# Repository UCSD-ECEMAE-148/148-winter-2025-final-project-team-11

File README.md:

# <div align="center">Autonomous Police Car</div>

### <div align="center"> ECE 148 Final Project </div>

#### <div align="center"> Team 11 Winter 2025 </div>

<div align="center">
    
</div>

## Table of Contents

  <ol>
    <li><a href="#team-members">Team Members</a></li>
    <li><a href="#abstract">Abstract</a></li>
    <li><a href="#what-we-promised">What We Promised</a></li>
    <li><a href="#accomplishments">Accomplishments</a></li>
    <li><a href="#challenges">Challenges</a></li>
    <li><a href="#final-project-videos">Final Project Videos</a></li>
    <li><a href="#hardware">Hardware</a></li>
    <li><a href="#software">Software</a></li>
        <ul>
            <li><a href="#slam-simultaneous-localization-and-mapping">SLAM (Simultaneous Localization and Mapping)</a></li>
            <li><a href="#obstacle-avoidance">Obstacle Avoidance</a></li>
        </ul>
    <li><a href="#gantt-chart">Gantt Chart</a></li>
    <li><a href="#course-deliverables">Course Deliverables</a></li>
    <li><a href="#project-reproduction">Project Reproduction</a></li>
    <li><a href="#acknowledgements">Acknowledgements</a></li>
  </ol>

<hr>

## Team Members

- MingWei Yeoh - ECE - 2025
- Trevor
- Minh Quach
- Jose

<hr>

## Abstract

An realistic looking autonomous car that can activate lights when it detects a speeding car and autonomously pull it over or initiate a chase.

Past MAE projects haven’t tried to use car following for a real task, nor make their autonomous car LOOK like an actual car.
Mechanically it will be a challenge to mount all the electronics inside of a small car body.

<hr>

## What We Promised

### Must Have

- LEDs
- Communication between LED controller and Jetson
- Body shell Mounting
- Chase the car
- Yolo running on OAK-D Camera

### Nice to Have

- Cool PCB
- Clean Electronics mounting
- A Siren
<hr>

## Accomplishments

- Follows car
- LEDs work great
- 150A Soft start power switch works great
<hr>

## Challenges

- Jetson not connecting to Wifi
- ROS2 not configured correctly to run our nodes
- I2C reaching bugged state
<hr>

## Final Project Videos

<hr>

## Hardware

Link to the OnShape [CAD](https://cad.onshape.com/documents/6c423dcbeb2588a9d7785133/w/5859bc8aee528f453679c661/e/83214a9dc768b66fa2069d19?renderMode=0&uiState=67d3caa0a720212af3f91fbd)

- **Green** - Body shell mounting method. It uses 8x3mm magnets.
- **Purple** - Reference geometry from the car
- **Black** - Structural 3D Printed pieces
- **Orange** - 3D Printed Spacers

The design is super clean and allows the body shell to easily cover all the electronics.

**Additional Hardware Necessary**

- Custom LED driver PCB
- Custom LED module
- 8x3mm Magnets
- 3mm bolts
- Body shell

## PCB

### High Level Overview

- Embedded EPS32S3
- USB C Port
- Anti spark power switch capable of 150 A
- Buzzer (for siren)
- 2x High Powered led driver
- 3x WS2815 Led Controllers
- Communication with Jetson via I2C
- 3 Spare GPIOs (if needed)
- Onboard VBAT -> 3V3 Buck regulator

**Power**
Snippet from the schematic. 3 Low RDson PMOS' act like the switch. When the on button is pressed, the 4s Lipo gets fed into the onboard buck regulator to power the microcontroller.

### Assembly

Hand Assembled. Theres a lot of parts

### Bringup

**LEDS**

</br>

**I2C**
ESP32 acts as a peripheral device with address 0x55. It takes in a 2 byte command. 0x00 and 0x11.
0x00 Turns on LEDs and 0x11 turns off LEDs.

## Software - Robocar Visual Pursuit Package

A ROS2 package for autonomous vehicle pursuit using computer vision and DepthAI. This package enables a robocar to detect and follow another vehicle using visual tracking.

### Table of Contents

- [Features](#features)
- [Prerequisites](#prerequisites)
- [Installation](#installation)
- [Nodes](#nodes)
  - [Car Detection Node](#car-detection-node)
  - [Lane Guidance Node](#lane-guidance-node)
  - [Parameter Tuner Node](#parameter-tuner-node)
- [Topics](#topics)
- [Launch Files](#launch-files)
- [Parameter Tuning](#parameter-tuning)
- [Troubleshooting](#troubleshooting)
- [Configuration Files](#configuration-files)

### Features

- Real-time car detection using YOLO and DepthAI
- Adaptive PID-based steering control
- Dynamic throttle management
- Real-time parameter tuning interface
- Parameter persistence across launches
- Robust tracking with lost-frame handling

### Prerequisites

- ROS2
- DepthAI
- OpenCV
- Python 3.8+

### Installation

1. Clone this repository into your ROS2 workspace:

```bash
cd ~/ros2_ws/src
git clone <repository_url> robocar_visual_pursuit_pkg
```

2. Install dependencies:

```bash
cd ~/ros2_ws
rosdep install --from-paths src --ignore-src -r -y
```

3. Build the package:

```bash
colcon build --packages-select robocar_visual_pursuit_pkg
```

### Nodes

#### Car Detection Node

The car detection node uses YOLO and DepthAI to detect vehicles in the camera feed and calculate their position relative to the robot.

**Parameters:**

- `confidence_threshold` (0.0-1.0): Confidence threshold for car detection
- `camera_centerline` (0.0-1.0): Normalized position of camera centerline
- `error_threshold` (0.0-1.0): Error threshold for steering control
- `iou_threshold` (0.0-1.0): IOU threshold for object detection
- `max_lost_frames` (0-30): Maximum number of frames to track lost object

**Topics:**

- Subscribes: `/camera/color/image_raw` (sensor_msgs/Image)
- Publishes: `/centroid` (std_msgs/Float32)

#### Lane Guidance Node

The lane guidance node implements PID control for steering and adaptive throttle management based on tracking error.

**Parameters:**

- `Kp_steering` (0.0-5.0): Proportional gain for steering control
- `Ki_steering` (0.0-2.0): Integral gain for steering control
- `Kd_steering` (0.0-2.0): Derivative gain for steering control
- `max_throttle` (0.0-1.0): Maximum throttle value
- `min_throttle` (0.0-0.5): Minimum throttle value

**Topics:**

- Subscribes: `/centroid` (std_msgs/Float32)
- Publishes: `/cmd_vel` (geometry_msgs/Twist)

#### Parameter Tuner Node

A dedicated node for real-time parameter tuning with persistent storage.

**Features:**

- Real-time parameter adjustment via rqt_reconfigure
- Parameter persistence across launches
- Automatic parameter forwarding to relevant nodes

### Topics

| Topic                     | Type                | Description                              |
| ------------------------- | ------------------- | ---------------------------------------- |
| `/camera/color/image_raw` | sensor_msgs/Image   | Raw camera feed                          |
| `/centroid`               | std_msgs/Float32    | Normalized target position (-1.0 to 1.0) |
| `/cmd_vel`                | geometry_msgs/Twist | Vehicle control commands                 |

### Launch Files

#### Car Pursuit Launch

Launch the complete visual pursuit system:

```bash
ros2 launch robocar_visual_pursuit_pkg car_pursuit_launch.py
```

This launches:

- Car detection node
- Lane guidance node
- Parameter tuner node
- VESC interface node

### Parameter Management

Parameters are managed through ROS2's rqt dynamic reconfigure system and YAML configuration files. The default parameters are stored in `config/default_params.yaml`.

#### Available Parameters

- `camera_centerline` (float, default: 0.5): Normalized position of camera centerline
- `confidence_threshold` (float, default: 0.2): Confidence threshold for car detection
- `debug_cv` (int, default: 0): Enable/disable debug visualization
- `error_threshold` (float, default: 0.5): Error threshold for steering control
- `iou_threshold` (float, default: 0.5): IOU threshold for object detection
- `max_lost_frames` (int, default: 30): Maximum number of frames to track lost object
- `model_path` (string): Path to YOLO model weights
- `use_sim_time` (bool, default: false): Use simulation time

#### Parameter Tuning

1. Launch the visual pursuit node:

```bash
ros2 launch robocar_visual_pursuit_pkg visual_pursuit.launch.py
```

2. Open rqt reconfigure:

```bash
ros2 run rqt_reconfigure rqt_reconfigure
```

3. Adjust parameters in real-time using the rqt interface

4. Export current parameters to YAML:

```bash
ros2 param dump /visual_pursuit_node > config/my_params.yaml
```

5. Load custom parameters at launch:

```bash
ros2 launch robocar_visual_pursuit_pkg visual_pursuit.launch.py params_file:=config/my_params.yaml
```

Note: You may need to consolidate the yaml params from multiple files as params dump specific to their own node but all nodes read from default_params.yaml by default. This will be fixed in a future update

### Troubleshooting

Common issues and solutions:

1. **Parameter Changes Not Saving**

   - Verify rqt_reconfigure is running
   - Check write permissions in the config directory
   - Ensure the parameter dump command executed successfully

2. **Node Not Starting**

   - Check if all required configuration files exist
   - Verify file paths in launch files
   - Ensure ROS2 environment is properly sourced

3. **Detection Issues**
   - Verify camera connection and permissions
   - Check model path in configuration
   - Adjust confidence and IOU thresholds

For additional help, check the ROS2 logs:

```bash
ros2 log info /visual_pursuit_node
```

### Configuration Files

The package uses several configuration files in the `config` directory:

- `default_params.yaml`: Default parameters for the visual pursuit system
- `car_detection_node`: Configuration for car detection parameters
- `lane_guidence`: Lane guidance system configuration
- `ros_racer_calibration.yaml`: Calibration parameters for the robocar

#### Configuration Structure

Each configuration file serves a specific purpose:

1. **Visual Pursuit Parameters** (`default_params.yaml`)

   - Core parameters for the visual pursuit system
   - Modified through rqt_reconfigure
   - Can be exported and loaded at runtime

2. **Car Detection Configuration** (`car_detection_node`)

   - YOLO model configuration
   - Detection thresholds and parameters
   - Camera settings

3. **Lane Guidance Configuration** (`lane_guidence`)

   - Lane detection parameters
   - Steering control settings
   - PID tuning values

4. **Calibration Parameters** (`ros_racer_calibration.yaml`)
   - Hardware-specific calibration
   - Motor and servo settings
   - Sensor calibration values

To modify these configurations:

1. Use rqt_reconfigure for real-time parameter tuning
2. Export modified parameters to YAML files
3. Load specific configuration files at launch time

Example of loading multiple configuration files:

```bash
ros2 launch robocar_visual_pursuit_pkg visual_pursuit.launch.py \
  params_file:=config/my_params.yaml \
  calibration_file:=config/ros_racer_calibration.yaml
```

## Gantt Chart

## Course Deliverables

Here are our autonomous laps as part of our class deliverables:

- DonkeyCar Reinforcement Laps: https://youtube.com/shorts/6msSXXdx4cQ?feature=share
- GPS Laps: https://youtu.be/pAPebhBlGDo
- Lane Following: https://youtu.be/QzcPgDxxi5c

- All Slides: https://drive.google.com/drive/folders/1qeRSDj4K1PtiiYxJ_8OacECK8fxUN1bn?usp=sharing

## Acknowledgements

Special thanks to Alex and Winston!

<hr>

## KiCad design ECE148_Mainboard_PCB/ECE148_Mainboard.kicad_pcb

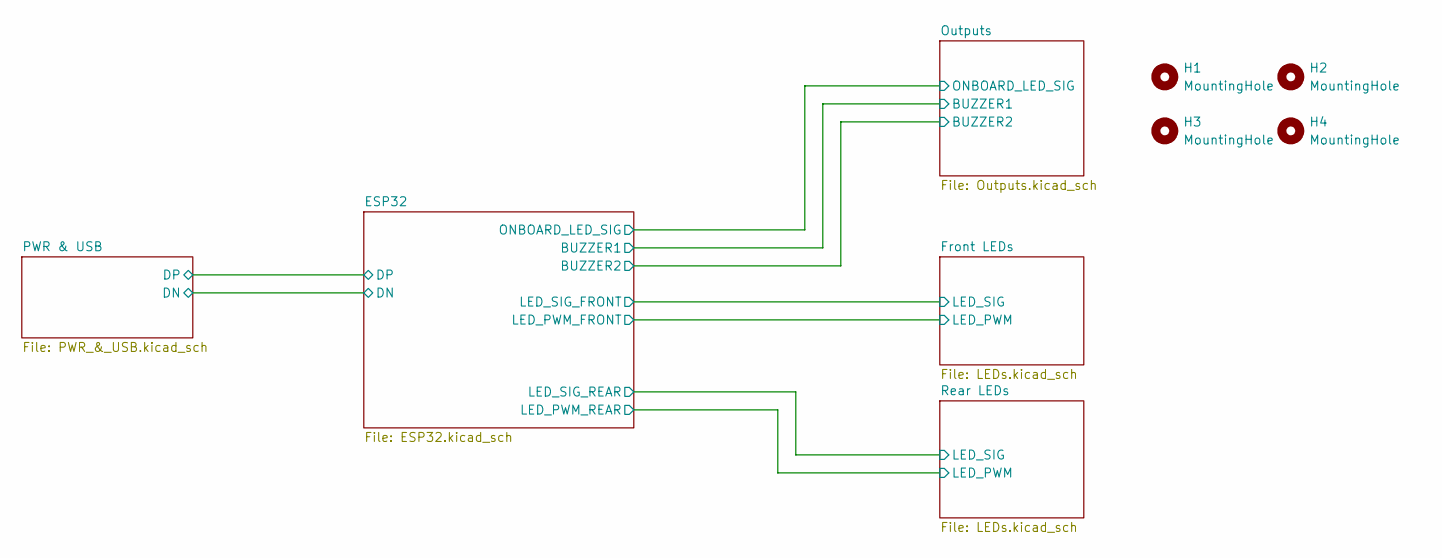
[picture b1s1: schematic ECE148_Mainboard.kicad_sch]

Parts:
H1, H2, H3, H4: MountingHole; MountingHole_3.2mm_M3

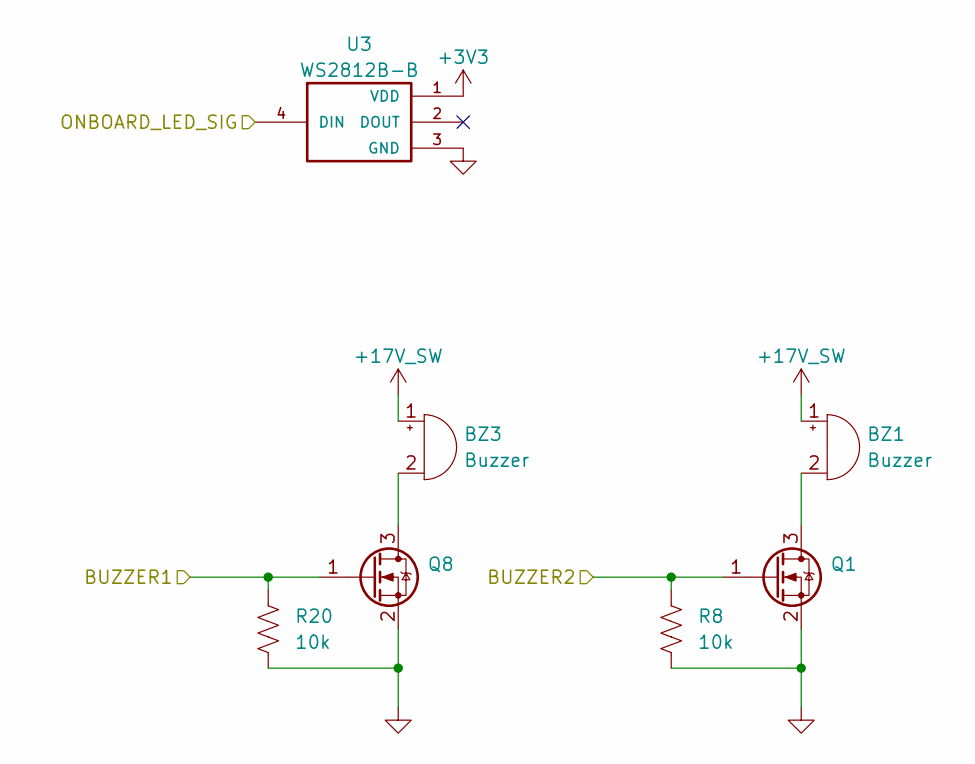
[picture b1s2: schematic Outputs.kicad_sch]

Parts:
BZ1, BZ3: Buzzer; Buzzer_12x9.5RM7.6
Q1, Q8: Q_NMOS_GSD; SOT-23
R8, R20: 10k; R_0402_1005Metric
U3: WS2812B-B; LED_WS2812B-B; PARTREV 5

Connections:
+3V3: U3.1 (VDD); also elsewhere on the board
+17V_SW: BZ1.1 (+), BZ3.1 (+); also elsewhere on the board
/ESP32/BUZZER1: Q8.1 (G), R20.1; also elsewhere on the board
/ESP32/BUZZER2: Q1.1 (G), R8.1; also elsewhere on the board
/ESP32/ONBOARD_LED_SIG: U3.4 (DIN); also elsewhere on the board
GND: Q1.2 (S), Q8.2 (S), R8.2, R20.2, U3.3 (GND); also elsewhere on the board
unnamed: BZ1.2 (-), Q1.3 (D)

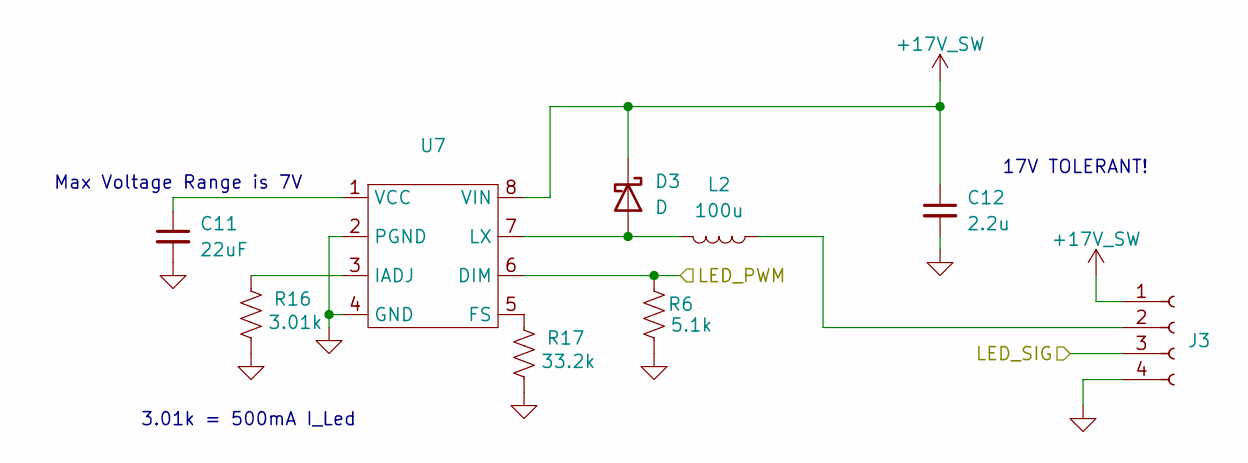
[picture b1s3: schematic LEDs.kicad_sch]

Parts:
C11: 22uF; C_0603_1608Metric
C12: 2.2u; C_0603_1608Metric
D3: D; D_SOD-123F
J3: Conn_01x05_Socket; JST_XH_B4B-XH-A_1x04_P2.50mm_Vertical
L2: 100u; L_Taiyo-Yuden_NR-60xx
R6: 5.1k; R_0402_1005Metric
R16: 3.01k; R_0402_1005Metric
R17: 33.2k; R_0402_1005Metric
U7: TI_SO-PowerPAD-8_ThermalVias

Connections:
+17V_SW: C12.1, D3.1 (K), J3.1, U7.8 (VIN); also elsewhere on the board
/ESP32/LED_PWM_FRONT: R6.1, U7.6 (DIM); also elsewhere on the board
/ESP32/LED_SIG_FRONT: J3.3; also elsewhere on the board
GND: C11.2, C12.2, J3.4, R6.2, R16.1, R17.1, U7.2 (PGND), U7.4 (GND), U7.9 (GND); also elsewhere on the board
unnamed: D3.2 (A), L2.2, U7.7 (LX)
unnamed: J3.2, L2.1
unnamed: R17.2, U7.5 (FS)
unnamed: R16.2, U7.3 (IADJ)
unnamed: C11.1, U7.1 (VCC)

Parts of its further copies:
C13: 22uF; C_0603_1608Metric
C14: 2.2u; C_0603_1608Metric
D4: D; D_SOD-123F
J12: Conn_01x05_Socket; JST_XH_B4B-XH-A_1x04_P2.50mm_Vertical
L3: 100u; L_Taiyo-Yuden_NR-60xx
R7: 5.1k; R_0402_1005Metric
R18: 3.01k; R_0402_1005Metric
R19: 33.2k; R_0402_1005Metric
U8: TI_SO-PowerPAD-8_ThermalVias

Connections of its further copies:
+17V_SW: C14.1, D4.1 (K), J12.1, U8.8 (VIN); also elsewhere on the board
/ESP32/LED_PWM_REAR: R7.1, U8.6 (DIM); also elsewhere on the board
/ESP32/LED_SIG_REAR: J12.3; also elsewhere on the board
GND: C13.2, C14.2, J12.4, R7.2, R18.1, R19.1, U8.2 (PGND), U8.4 (GND), U8.9 (GND); also elsewhere on the board
unnamed: D4.2 (A), L3.2, U8.7 (LX)
unnamed: J12.2, L3.1
unnamed: R19.2, U8.5 (FS)
unnamed: R18.2, U8.3 (IADJ)
unnamed: C13.1, U8.1 (VCC)

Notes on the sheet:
17V TOLERANT!
Max Voltage Range is 7V
3.01k = 500mA I_Led

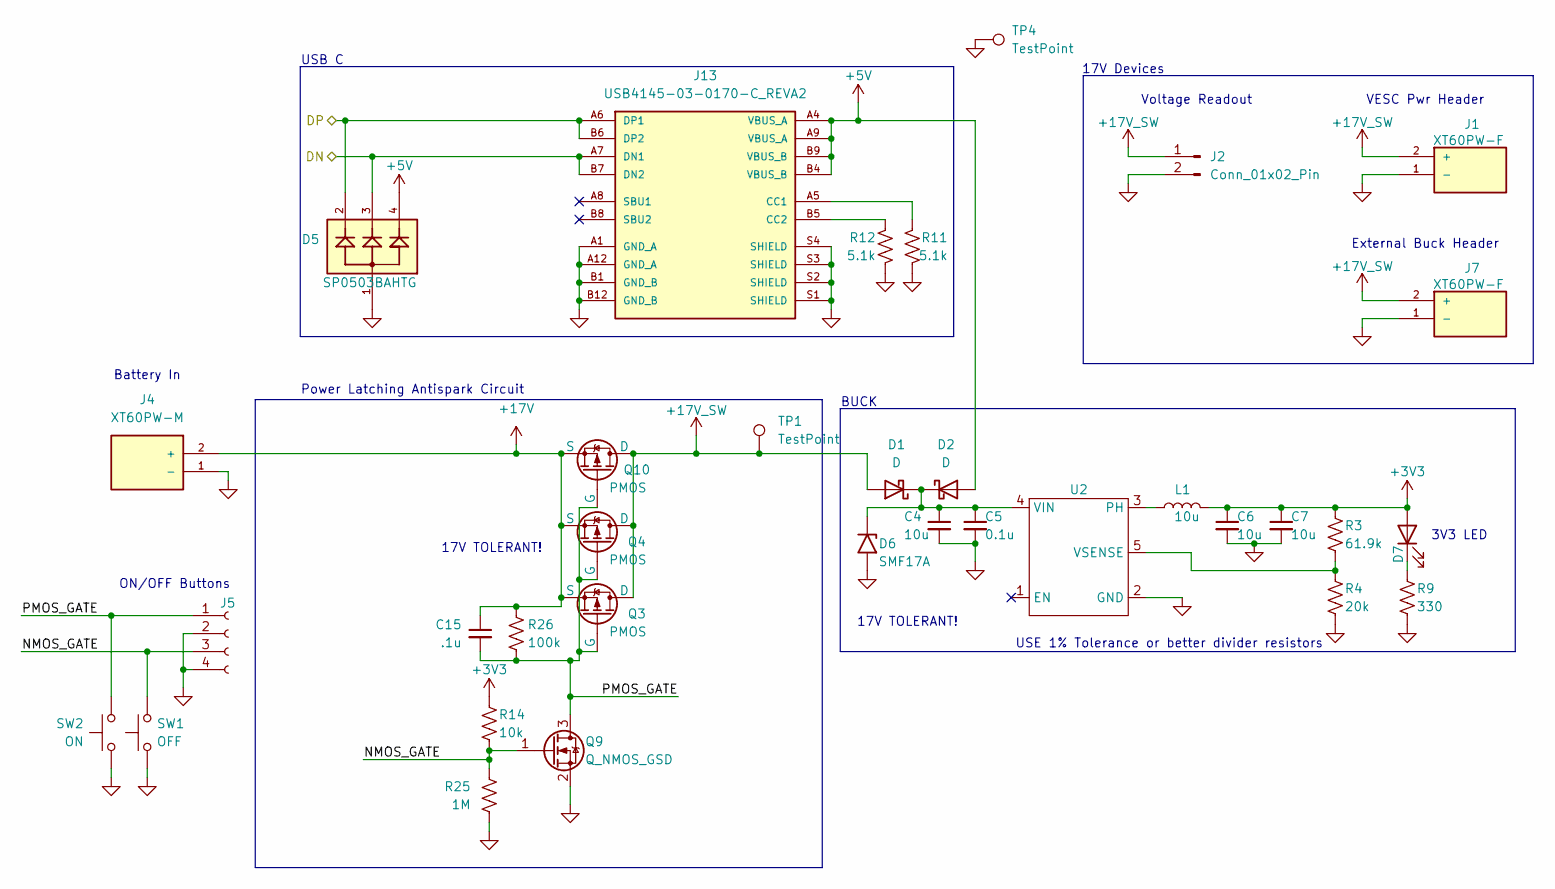
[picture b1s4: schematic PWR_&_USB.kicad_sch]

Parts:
C4, C6, C7: 10u; C_0805_2012Metric
C5: 0.1u; C_0402_1005Metric
C15: .1u; C_0402_1005Metric
D1, D2: D; D_SOD-123F
D5: SP0503BAHTG; SOT-143; PARTREV N/A
D6: SMF17A; D_SOD-123F
D7: LED; LED_0603_1608Metric
J1, J7: XT60PW-F; AMASS_XT60PW-F_1x02_P7.20mm_Horizontal; PARTREV V1.2
J2: Conn_01x02_Pin; PinHeader_1x02_P2.54mm_Vertical
J4: XT60PW-M; AMASS_XT60PW-M_1x02_P7.20mm_Horizontal; PARTREV V1.2
J5: Conn_01x04_Socket; PinHeader_1x04_P2.54mm_Vertical
J13: USB4145-03-0170-C_REVA2; GCT_USB4145-03-0170-C_REVA2; PARTREV A2
L1: 10u; L_Wurth_WE-LQSH-2010
Q3, Q4, Q10: PMOS; PowerPAK_SO-8_Single
Q9: Q_NMOS_GSD; SOT-23
R3: 61.9k; R_0402_1005Metric
R4: 20k; R_0402_1005Metric
R9: 330; R_0402_1005Metric
R11, R12: 5.1k; R_0402_1005Metric
R14: 10k; R_0402_1005Metric
R25: 1M; R_0402_1005Metric
R26: 100k; R_0402_1005Metric
SW1: OFF; SW_Push_1P1T_NO_Vertical_Wuerth_434133025816
SW2: ON; SW_Push_1P1T_NO_Vertical_Wuerth_434133025816
TP1, TP4: TestPoint; TestPoint_Pad_D1.5mm
U2: SOT-23-5

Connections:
+3V3: C6.1, C7.1, D7.2 (A), L1.2, R3.1, R14.1; also elsewhere on the board
+5V: D2.2 (A), D5.4, J13.A4 (VBUS_A), J13.A9 (VBUS_A), J13.B4 (VBUS_B), J13.B9 (VBUS_B)
+17V: C15.1, J4.2 (+), Q3.1 (S), Q3.2 (S), Q3.3 (S), Q4.1 (S), Q4.2 (S), Q4.3 (S), Q10.1 (S), Q10.2 (S), Q10.3 (S), R26.1
+17V_SW: D1.2 (A), J1.2 (+), J2.1, J7.2 (+), Q3.5 (D), Q4.5 (D), Q10.5 (D), TP1.1; also elsewhere on the board
/ESP32/DN: D5.3, J13.A7 (DN1), J13.B7 (DN2); also elsewhere on the board
/ESP32/DP: D5.2, J13.A6 (DP1), J13.B6 (DP2); also elsewhere on the board
/PWR & USB/NMOS_GATE: J5.3, Q9.1 (G), R14.2, R25.1, SW1.2
/PWR & USB/PMOS_GATE: C15.2, J5.1, Q3.4 (G), Q4.4 (G), Q9.3 (D), Q10.4 (G), R26.2, SW2.1
GND: C4.2, C5.2, C6.2, C7.2, D5.1, D6.2 (A2), J1.1 (-), J2.2, J4.1 (-), J5.2, J5.4, J7.1 (-), J13.A1 (GND_A), J13.A12 (GND_A), J13.B1 (GND_B), J13.B12 (GND_B), J13.S1 (SHIELD), J13.S2 (SHIELD), J13.S3 (SHIELD), J13.S4 (SHIELD), Q9.2 (S), R4.2, R9.2, R11.2, R12.2, R25.2, SW1.1, SW2.2, TP4.1, U2.2 (GND); also elsewhere on the board
unnamed: C4.1, C5.1, D1.1 (K), D2.1 (K), D6.1 (A1), U2.4 (VIN)
unnamed: D7.1 (K), R9.1
unnamed: J13.A5 (CC1), R11.1
unnamed: J13.B5 (CC2), R12.1
unnamed: L1.1, U2.3 (PH)
unnamed: R3.2, R4.1, U2.5 (VSENSE)

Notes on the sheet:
Battery In
BUCK
3V3 LED
VESC Pwr Header
USE 1% Tolerance or better divider resistors
Power Latching Antispark Circuit
17V TOLERANT!
USB C
External Buck Header
Voltage Readout
17V Devices
ON/OFF Buttons

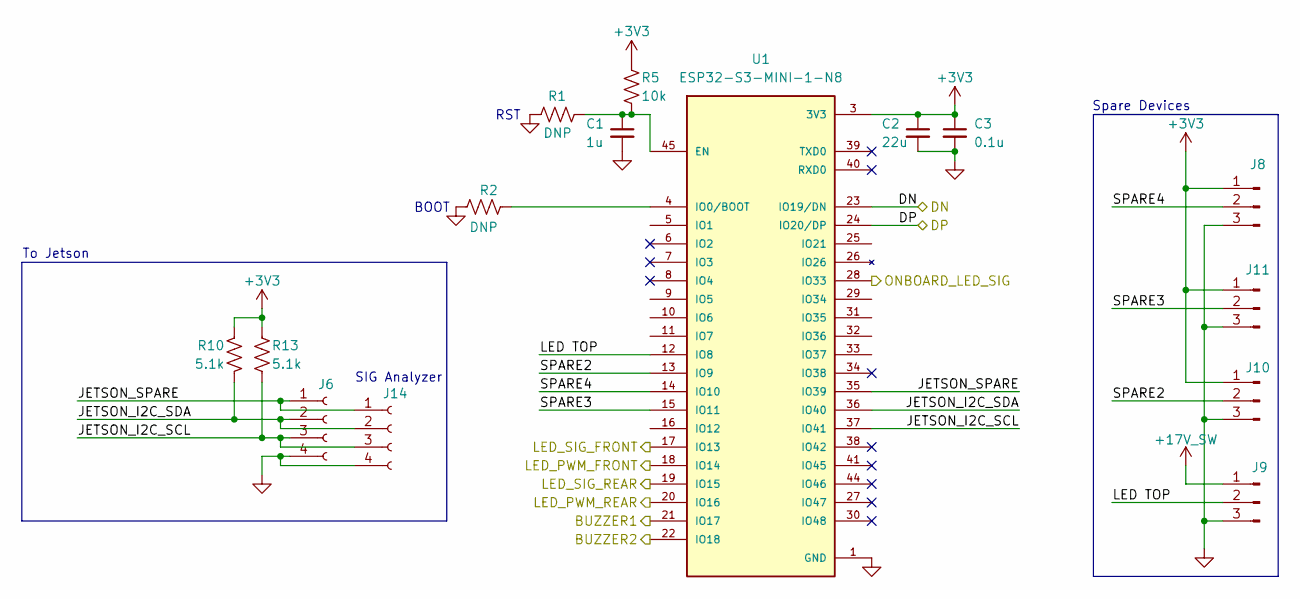
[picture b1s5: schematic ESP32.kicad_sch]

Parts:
C1: 1u; C_0402_1005Metric
C2: 22u; C_0603_1608Metric
C3: 0.1u; C_0402_1005Metric
J6: Conn_01x04_Socket; JST_XH_B4B-XH-A_1x04_P2.50mm_Vertical
J8, J9, J10, J11: Conn_01x03_Pin; PinHeader_1x03_P2.54mm_Vertical
J14: Conn_01x04_Socket; PinHeader_1x04_P2.54mm_Vertical
R1, R2: DNP; R_0402_1005Metric
R5: 10k; R_0402_1005Metric
R10, R13: 5.1k; R_0402_1005Metric
U1: ESP32-S3-MINI-1-N8; XCVR_ESP32-S3-MINI-1-N8; PARTREV v0.6

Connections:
+3V3: C2.1, C3.1, J8.1, J10.1, J11.1, R5.1, R10.1, R13.1, U1.3 (3V3); also elsewhere on the board
+17V_SW: J9.1; also elsewhere on the board
/ESP32/BUZZER1: U1.21 (IO17); also elsewhere on the board
/ESP32/BUZZER2: U1.22 (IO18); also elsewhere on the board
/ESP32/DN: U1.23 (IO19/DN); also elsewhere on the board
/ESP32/DP: U1.24 (IO20/DP); also elsewhere on the board
/ESP32/JETSON_I2C_SCL: J6.3, J14.3, R13.2, U1.37 (IO41)
/ESP32/JETSON_I2C_SDA: J6.2, J14.2, R10.2, U1.36 (IO40)
/ESP32/JETSON_SPARE: J6.1, J14.1, U1.35 (IO39)
/ESP32/LED TOP: J9.2, U1.12 (IO8)
/ESP32/LED_PWM_FRONT: U1.18 (IO14); also elsewhere on the board
/ESP32/LED_PWM_REAR: U1.20 (IO16); also elsewhere on the board
/ESP32/LED_SIG_FRONT: U1.17 (IO13); also elsewhere on the board
/ESP32/LED_SIG_REAR: U1.19 (IO15); also elsewhere on the board
/ESP32/ONBOARD_LED_SIG: U1.28 (IO33); also elsewhere on the board
/ESP32/SPARE2: J10.2, U1.13 (IO9)
/ESP32/SPARE3: J11.2, U1.15 (IO11)
/ESP32/SPARE4: J8.2, U1.14 (IO10)
GND: C1.2, C2.2, C3.2, J6.4, J8.3, J9.3, J10.3, J11.3, J14.4, R1.1, R2.1, U1.1 (GND), U1.2 (GND), U1.42 (GND), U1.43 (GND), U1.46 (GND), U1.47 (GND), U1.48 (GND), U1.49 (GND), U1.50 (GND), U1.51 (GND), U1.52 (GND), U1.53 (GND), U1.54 (GND), U1.55 (GND), U1.56 (GND), U1.57 (GND), U1.58 (GND), U1.59 (GND), U1.60 (GND), U1.61 (GND), U1.61_1 (GND), U1.61_2 (GND), U1.61_3 (GND), U1.61_4 (GND), U1.61_5 (GND), U1.61_6 (GND), U1.61_7 (GND), U1.61_8 (GND), U1.62 (GND), U1.63 (GND), U1.64 (GND), U1.65 (GND); also elsewhere on the board
unnamed: C1.1, R1.2, R5.2, U1.45 (EN)
unnamed: R2.2, U1.4 (IO0/BOOT)

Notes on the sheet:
BOOT
SIG Analyzer
Spare Devices
RST
To Jetson

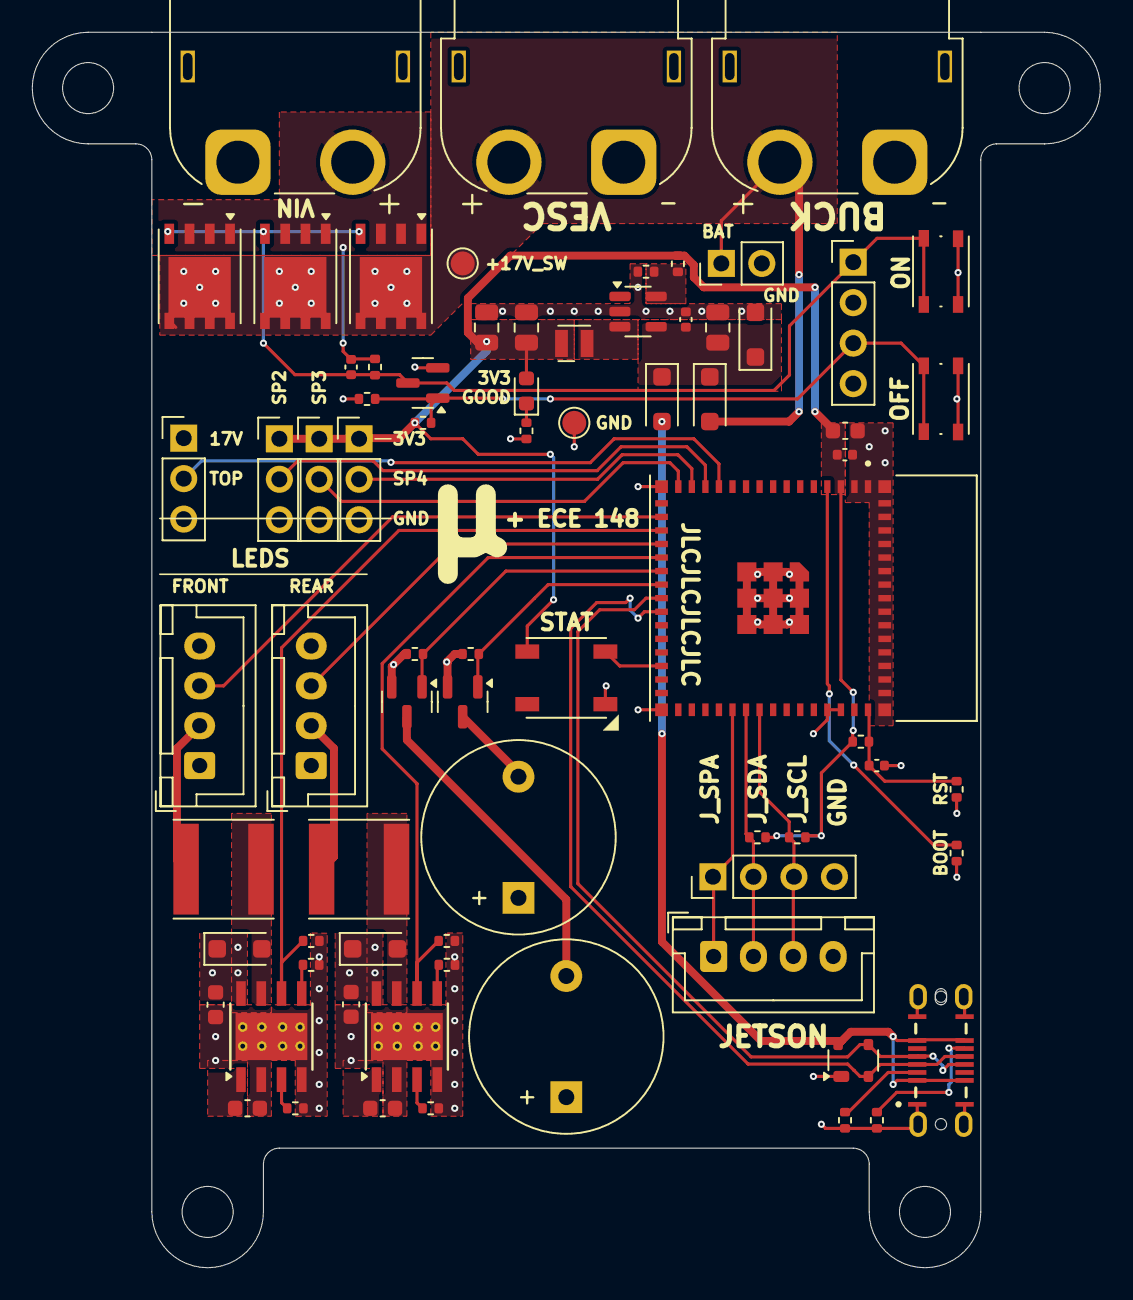
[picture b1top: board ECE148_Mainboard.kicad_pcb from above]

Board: 4 copper layers, 67.0 x 77.5 mm, 78 parts (0 on the bottom side), 42 nets.

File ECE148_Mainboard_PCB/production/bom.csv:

Designator,Footprint,Quantity,Value,LCSC Part #
"BZ1, BZ3",Buzzer_12x9.5RM7.6,2,Buzzer,
C1,0402,1,1u,
"C11, C13",0603,2,22uF,
"C12, C14",0603,2,2.2u,
C15,0402,1,.1u,
C2,0603,1,22u,
"C3, C5",0402,2,0.1u,
"C4, C6, C7",0805,3,10u,
"D1, D2, D3, D4",D_SOD-123F,4,D,
D5,SOT-143,1,SP0503BAHTG,
D6,D_SOD-123F,1,SMF17A,
D7,0603,1,LED,
"J1, J7",AMASS_XT60PW-F_1x02_P7.20mm_Horizontal,2,XT60PW-F,
"J10, J11, J8, J9",PinHeader_1x03_P2.54mm_Vertical,4,Conn_01x03_Pin,
"J12, J3",JST_XH_B4B-XH-A_1x04_P2.50mm_Vertical,2,Conn_01x05_Socket,
J13,GCT_USB4145-03-0170-C_REVA2,1,USB4145-03-0170-C_REVA2,
"J14, J5",PinHeader_1x04_P2.54mm_Vertical,2,Conn_01x04_Socket,
J2,PinHeader_1x02_P2.54mm_Vertical,1,Conn_01x02_Pin,
J4,AMASS_XT60PW-M_1x02_P7.20mm_Horizontal,1,XT60PW-M,
J6,JST_XH_B4B-XH-A_1x04_P2.50mm_Vertical,1,Conn_01x04_Socket,
L1,L_Wurth_WE-LQSH-2010,1,10u,
"L2, L3",L_Taiyo-Yuden_NR-60xx,2,100u,
"Q1, Q8, Q9",SOT-23,3,Q_NMOS_GSD,
"Q10, Q3, Q4",PowerPAK_SO-8_Single,3,PMOS,
"R1, R2",0402,2,DNP,
"R10, R11, R12, R13, R6, R7",0402,6,5.1k,
"R14, R20, R5, R8",0402,4,10k,
"R16, R18",0402,2,3.01k,
"R17, R19",0402,2,33.2k,
R25,0402,1,1M,
R26,0402,1,100k,
R3,0402,1,61.9k,
R4,0402,1,20k,
R9,0402,1,330,
SW1,SW_Push_1P1T_NO_Vertical_Wuerth_434133025816,1,OFF,
SW2,SW_Push_1P1T_NO_Vertical_Wuerth_434133025816,1,ON,
"TP1, TP4",TestPoint_Pad_D1.5mm,2,TestPoint,
U1,XCVR_ESP32-S3-MINI-1-N8,1,ESP32-S3-MINI-1-N8,
U2,SOT-23-5,1,~,
U3,LED_WS2812B-B,1,WS2812B-B,
"U7, U8",TI_SO-PowerPAD-8_ThermalVias,2,~,

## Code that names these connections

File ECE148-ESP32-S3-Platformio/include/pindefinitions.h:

#define LED_TOP 8
#define ONBOARD_LED 33
#define LED_SIG_FRONT 13
#define LED_PWM_FRONT 14
#define LED_SIG_REAR 15
#define LED_PWM_REAR 16
#define BUZZER1 17
#define BUZZER2 18

#define NUM_LEDS 11

#define JETSON_SPARE 39
#define JETSON_I2C_SDA 40
#define JETSON_I2C_SCL 41

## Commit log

2025-03-14 markdown writeup mostly done. Added esp32 schematic and code
2025-03-14 fixed formatting
2025-03-17 Add video
2025-03-20 Embed Youtube Video
2025-03-21 Updated README with new parameter setting process
